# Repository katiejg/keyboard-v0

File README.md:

# keyboard_v0

## Guides Followed
- [Masterzen](https://www.masterzen.fr/tag/#mechanical-keyboards)
- [ai03](https://wiki.ai03.com/books/pcb-design)

## References
- [K6 Keycap Layout](https://www.keychron.com/pages/keychron-k6-keyboard-keycaps-layout-and-keycap-size-hd-picture)

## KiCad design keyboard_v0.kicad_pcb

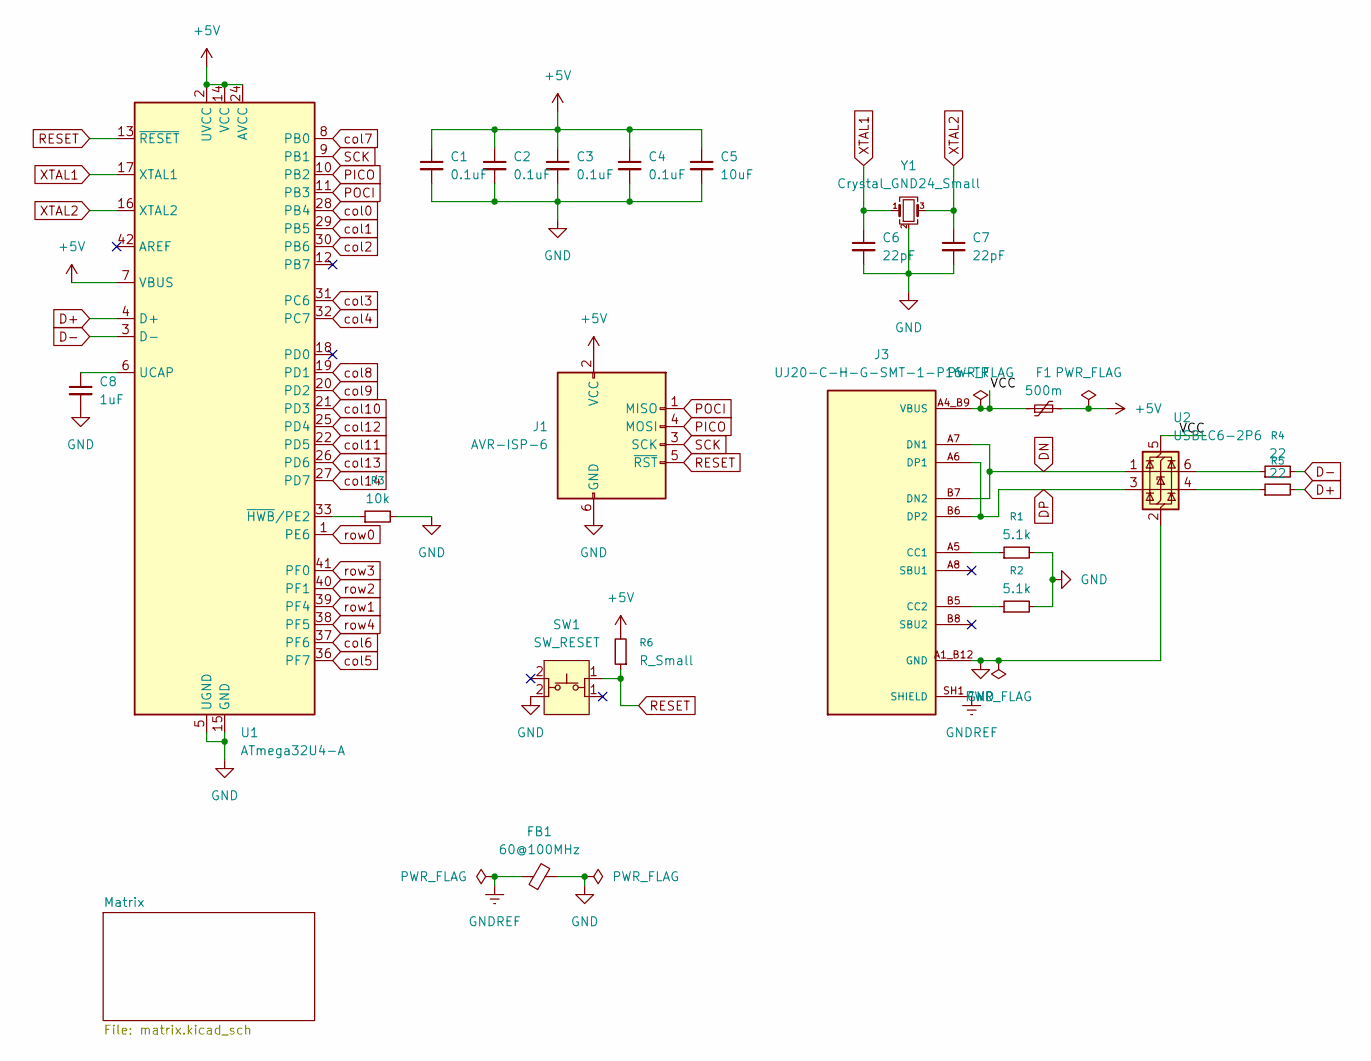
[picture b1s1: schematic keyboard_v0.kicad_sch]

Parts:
C1, C2, C3, C4: 0.1uF; C_0805_2012Metric_Pad1.18x1.45mm_HandSolder
C5: 10uF; C_0805_2012Metric_Pad1.18x1.45mm_HandSolder
C6, C7: 22pF; C_0805_2012Metric_Pad1.18x1.45mm_HandSolder
C8: 1uF; C_0805_2012Metric_Pad1.18x1.45mm_HandSolder
F1: 500m; Fuse_1206_3216Metric_Pad1.42x1.75mm_HandSolder
FB1: 60@100MHz; L_0805_2012Metric_Pad1.05x1.20mm_HandSolder
J1: AVR-ISP-6; Reset_Pretty-Mask
J3: UJ20-C-H-G-SMT-1-P16-TR; SAMESKY_UJ20-C-H-G-SMT-1-P16-TR; PARTREV 1.0; DigiKey_Part_Number 2223-UJ20-C-H-G-SMT-1-P16-TRCT-ND
R1, R2: 5.1k; R_0805_2012Metric_Pad1.20x1.40mm_HandSolder
R3: 10k; R_0805_2012Metric_Pad1.20x1.40mm_HandSolder
R4, R5: 22; R_0805_2012Metric_Pad1.20x1.40mm_HandSolder
R6: R_Small; R_0805_2012Metric_Pad1.20x1.40mm_HandSolder
SW1: SW_RESET; SW_SPST_SKQG_WithStem
U1: ATmega32U4-A; TQFP-44_10x10mm_P0.8mm
U2: USBLC6-2P6; SOT-666
Y1: Crystal_GND24_Small; Crystal_SMD_3225-4Pin_3.2x2.5mm_HandSoldering

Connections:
+5V: C1.1, C2.1, C3.1, C4.1, C5.1, F1.2, J1.2 (VCC), R6.2, U1.2 (UVCC), U1.7 (VBUS), U1.14 (VCC), U1.24 (AVCC), U1.34 (VCC), U1.44 (AVCC)
/VCC: F1.1, J3.A4_B9 (VBUS), J3.B4_A9 (VBUS), U2.5 (VBUS)
D+: R5.2, U1.4 (D+)
D-: R4.2, U1.3 (D-)
DN: J3.A7 (DN1), J3.B7 (DN2), U2.1 (I/O1)
DP: J3.A6 (DP1), J3.B6 (DP2), U2.3 (I/O2)
GND: C1.2, C2.2, C3.2, C4.2, C5.2, C6.2, C7.2, C8.2, FB1.2, J1.6 (GND), J3.A1_B12 (GND), J3.B1_A12 (GND), R1.2, R2.2, R3.2, SW1.2 (K), U1.5 (UGND), U1.15 (GND), U1.23 (GND), U1.35 (GND), U1.43 (GND), U2.2 (GND), Y1.2 (G), Y1.4 (G)
GNDREF: FB1.1, J3.SH1 (SHIELD), J3.SH2 (SHIELD), J3.SH3 (SHIELD), J3.SH4 (SHIELD)
unnamed: J3.A5 (CC1), R1.1
unnamed: J3.B5 (CC2), R2.1
unnamed: R4.1, U2.6 (I/O1)
unnamed: R5.1, U2.4 (I/O2)
unnamed: C8.1, U1.6 (UCAP)
unnamed: R3.1, U1.33 (~HWB/PE2)
PICO: J1.4 (MOSI), U1.10 (PB2)
POCI: J1.1 (MISO), U1.11 (PB3)
RESET: J1.5 (~RST), R6.1, SW1.1 (2), U1.13 (~RESET)
SCK: J1.3 (SCK), U1.9 (PB1)
XTAL1: C6.1, U1.17 (XTAL1), Y1.1
XTAL2: C7.1, U1.16 (XTAL2), Y1.3
col0: U1.28 (PB4); also elsewhere on the board
col1: U1.29 (PB5); also elsewhere on the board
col2: U1.30 (PB6); also elsewhere on the board
col3: U1.31 (PC6); also elsewhere on the board
col4: U1.32 (PC7); also elsewhere on the board
col5: U1.36 (PF7); also elsewhere on the board
col6: U1.37 (PF6); also elsewhere on the board
col7: U1.8 (PB0); also elsewhere on the board
col8: U1.19 (PD1); also elsewhere on the board
col9: U1.20 (PD2); also elsewhere on the board
col10: U1.21 (PD3); also elsewhere on the board
col11: U1.22 (PD5); also elsewhere on the board
col12: U1.25 (PD4); also elsewhere on the board
col13: U1.26 (PD6); also elsewhere on the board
col14: U1.27 (PD7); also elsewhere on the board
row0: U1.1 (PE6); also elsewhere on the board
row1: U1.39 (PF4); also elsewhere on the board
row2: U1.40 (PF1); also elsewhere on the board
row3: U1.41 (PF0); also elsewhere on the board
row4: U1.38 (PF5); also elsewhere on the board

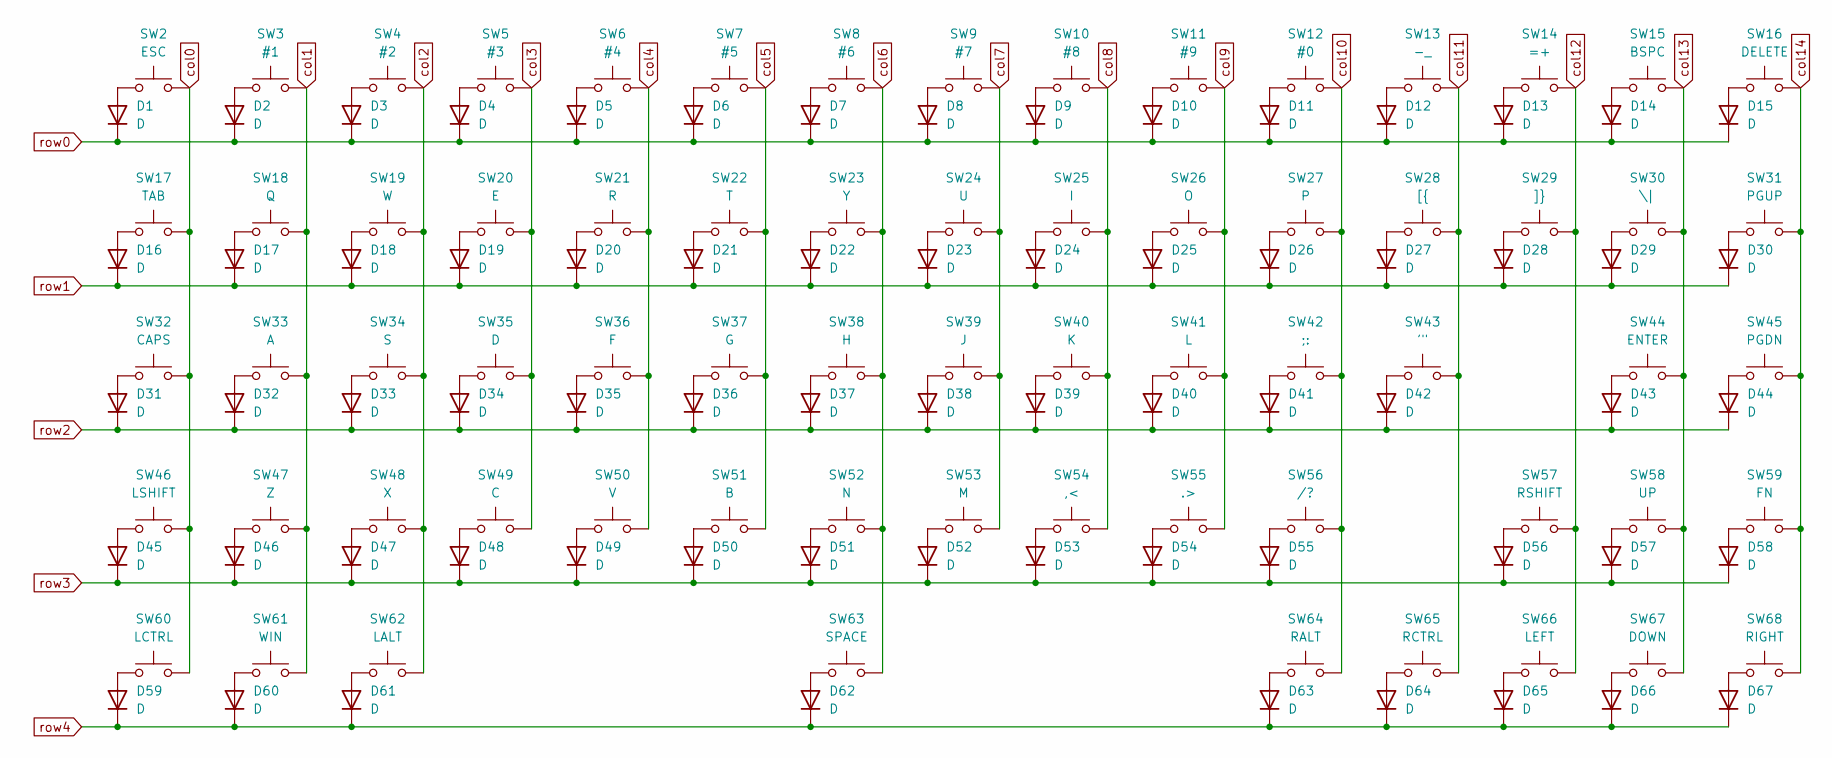
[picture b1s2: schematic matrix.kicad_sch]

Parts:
D1, D2, D3, D4, D5, D6, D7, D8, D9, D10, D11, D12, D13, D14, D15, D16, D17, D18, D19, D20, D21, D22, D23, D24, D25, D26, D27, D28, D29, D30, D31, D32, D33, D34, D35, D36, D37, D38, D39, D40, D41, D42, D43, D44, D45, D46, D47, D48, D49, D50, D51, D52, D53, D54, D55, D56, D57, D58, D59, D60, D61, D62, D63, D64, D65, D66, D67: D; D_SOD-123
SW2: ESC; MX-Hotswap-1U
SW3: #1; MX-Hotswap-1U
SW4: #2; MX-Hotswap-1U
SW5: #3; MX-Hotswap-1U
SW6: #4; MX-Hotswap-1U
SW7: #5; MX-Hotswap-1U
SW8: #6; MX-Hotswap-1U
SW9: #7; MX-Hotswap-1U
SW10: #8; MX-Hotswap-1U
SW11: #9; MX-Hotswap-1U
SW12: #0; MX-Hotswap-1U
SW13: -_; MX-Hotswap-1U
SW14: =+; MX-Hotswap-1U
SW15: BSPC; MX-Hotswap-2U
SW16: DELETE; MX-Hotswap-1U
SW17: TAB; MX-Hotswap-1.5U
SW18: Q; MX-Hotswap-1U
SW19: W; MX-Hotswap-1U
SW20: E; MX-Hotswap-1U
SW21: R; MX-Hotswap-1U
SW22: T; MX-Hotswap-1U
SW23: Y; MX-Hotswap-1U
SW24: U; MX-Hotswap-1U
SW25: I; MX-Hotswap-1U
SW26: O; MX-Hotswap-1U
SW27: P; MX-Hotswap-1U
SW28: [{; MX-Hotswap-1U
SW29: ]}; MX-Hotswap-1U
SW30: \|; MX-Hotswap-1.5U
SW31: PGUP; MX-Hotswap-1U
SW32: CAPS; MX-Hotswap-1.75U
SW33: A; MX-Hotswap-1U
SW34: S; MX-Hotswap-1U
SW35: D; MX-Hotswap-1U
SW36: F; MX-Hotswap-1U
SW37: G; MX-Hotswap-1U
SW38: H; MX-Hotswap-1U
SW39: J; MX-Hotswap-1U
SW40: K; MX-Hotswap-1U
SW41: L; MX-Hotswap-1U
SW42: ;:; MX-Hotswap-1U
SW43: '"; MX-Hotswap-1U
SW44: ENTER; MX-Hotswap-2.25U
SW45: PGDN; MX-Hotswap-1U
SW46: LSHIFT; MX-Hotswap-2.25U
SW47: Z; MX-Hotswap-1U
SW48: X; MX-Hotswap-1U
SW49: C; MX-Hotswap-1U
SW50: V; MX-Hotswap-1U
SW51: B; MX-Hotswap-1U
SW52: N; MX-Hotswap-1U
SW53: M; MX-Hotswap-1U
SW54: ,<; MX-Hotswap-1U
SW55: .>; MX-Hotswap-1U
SW56: /?; MX-Hotswap-1U
SW57: RSHIFT; MX-Hotswap-1.75U
SW58: UP; MX-Hotswap-1U
SW59: FN; MX-Hotswap-1U
SW60: LCTRL; MX-Hotswap-1.25U
SW61: WIN; MX-Hotswap-1.25U
SW62: LALT; MX-Hotswap-1.25U
SW63: SPACE; MX-Hotswap-6.25U
SW64: RALT; MX-Hotswap-1.25U
SW65: RCTRL; MX-Hotswap-1.25U
SW66: LEFT; MX-Hotswap-1U
SW67: DOWN; MX-Hotswap-1U
SW68: RIGHT; MX-Hotswap-1U

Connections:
unnamed: D1.2 (A), SW2.1
unnamed: D2.2 (A), SW3.1
unnamed: D3.2 (A), SW4.1
unnamed: D4.2 (A), SW5.1
unnamed: D5.2 (A), SW6.1
unnamed: D6.2 (A), SW7.1
unnamed: D7.2 (A), SW8.1
unnamed: D8.2 (A), SW9.1
unnamed: D9.2 (A), SW10.1
unnamed: D10.2 (A), SW11.1
unnamed: D11.2 (A), SW12.1
unnamed: D12.2 (A), SW13.1
unnamed: D13.2 (A), SW14.1
unnamed: D14.2 (A), SW15.1
unnamed: D15.2 (A), SW16.1
unnamed: D16.2 (A), SW17.1
unnamed: D17.2 (A), SW18.1
unnamed: D18.2 (A), SW19.1
unnamed: D19.2 (A), SW20.1
unnamed: D20.2 (A), SW21.1
unnamed: D21.2 (A), SW22.1
unnamed: D22.2 (A), SW23.1
unnamed: D23.2 (A), SW24.1
unnamed: D24.2 (A), SW25.1
unnamed: D25.2 (A), SW26.1
unnamed: D26.2 (A), SW27.1
unnamed: D27.2 (A), SW28.1
unnamed: D28.2 (A), SW29.1
unnamed: D29.2 (A), SW30.1
unnamed: D30.2 (A), SW31.1
unnamed: D31.2 (A), SW32.1
unnamed: D32.2 (A), SW33.1
unnamed: D33.2 (A), SW34.1
unnamed: D34.2 (A), SW35.1
unnamed: D35.2 (A), SW36.1
unnamed: D36.2 (A), SW37.1
unnamed: D37.2 (A), SW38.1
unnamed: D38.2 (A), SW39.1
unnamed: D39.2 (A), SW40.1
unnamed: D40.2 (A), SW41.1
unnamed: D41.2 (A), SW42.1
unnamed: D42.2 (A), SW43.1
unnamed: D43.2 (A), SW44.1
unnamed: D44.2 (A), SW45.1
unnamed: D45.2 (A), SW46.1
unnamed: D46.2 (A), SW47.1
unnamed: D47.2 (A), SW48.1
unnamed: D48.2 (A), SW49.1
unnamed: D49.2 (A), SW50.1
unnamed: D50.2 (A), SW51.1
unnamed: D51.2 (A), SW52.1
unnamed: D52.2 (A), SW53.1
unnamed: D53.2 (A), SW54.1
unnamed: D54.2 (A), SW55.1
unnamed: D55.2 (A), SW56.1
unnamed: D56.2 (A), SW57.1
unnamed: D57.2 (A), SW58.1
unnamed: D58.2 (A), SW59.1
unnamed: D59.2 (A), SW60.1
unnamed: D60.2 (A), SW61.1
unnamed: D61.2 (A), SW62.1
unnamed: D62.2 (A), SW63.1
unnamed: D63.2 (A), SW64.1
unnamed: D64.2 (A), SW65.1
unnamed: D65.2 (A), SW66.1
unnamed: D66.2 (A), SW67.1
unnamed: D67.2 (A), SW68.1
col0: SW2.2, SW17.2, SW32.2, SW46.2, SW60.2; also elsewhere on the board
col1: SW3.2, SW18.2, SW33.2, SW47.2, SW61.2; also elsewhere on the board
col2: SW4.2, SW19.2, SW34.2, SW48.2, SW62.2; also elsewhere on the board
col3: SW5.2, SW20.2, SW35.2, SW49.2; also elsewhere on the board
col4: SW6.2, SW21.2, SW36.2, SW50.2; also elsewhere on the board
col5: SW7.2, SW22.2, SW37.2, SW51.2; also elsewhere on the board
col6: SW8.2, SW23.2, SW38.2, SW52.2, SW63.2; also elsewhere on the board
col7: SW9.2, SW24.2, SW39.2, SW53.2; also elsewhere on the board
col8: SW10.2, SW25.2, SW40.2, SW54.2; also elsewhere on the board
col9: SW11.2, SW26.2, SW41.2, SW55.2; also elsewhere on the board
col10: SW12.2, SW27.2, SW42.2, SW56.2, SW64.2; also elsewhere on the board
col11: SW13.2, SW28.2, SW43.2, SW65.2; also elsewhere on the board
col12: SW14.2, SW29.2, SW57.2, SW66.2; also elsewhere on the board
col13: SW15.2, SW30.2, SW44.2, SW58.2, SW67.2; also elsewhere on the board
col14: SW16.2, SW31.2, SW45.2, SW59.2, SW68.2; also elsewhere on the board
row0: D1.1 (K), D2.1 (K), D3.1 (K), D4.1 (K), D5.1 (K), D6.1 (K), D7.1 (K), D8.1 (K), D9.1 (K), D10.1 (K), D11.1 (K), D12.1 (K), D13.1 (K), D14.1 (K), D15.1 (K); also elsewhere on the board
row1: D16.1 (K), D17.1 (K), D18.1 (K), D19.1 (K), D20.1 (K), D21.1 (K), D22.1 (K), D23.1 (K), D24.1 (K), D25.1 (K), D26.1 (K), D27.1 (K), D28.1 (K), D29.1 (K), D30.1 (K); also elsewhere on the board
row2: D31.1 (K), D32.1 (K), D33.1 (K), D34.1 (K), D35.1 (K), D36.1 (K), D37.1 (K), D38.1 (K), D39.1 (K), D40.1 (K), D41.1 (K), D42.1 (K), D43.1 (K), D44.1 (K); also elsewhere on the board
row3: D45.1 (K), D46.1 (K), D47.1 (K), D48.1 (K), D49.1 (K), D50.1 (K), D51.1 (K), D52.1 (K), D53.1 (K), D54.1 (K), D55.1 (K), D56.1 (K), D57.1 (K), D58.1 (K); also elsewhere on the board
row4: D59.1 (K), D60.1 (K), D61.1 (K), D62.1 (K), D63.1 (K), D64.1 (K), D65.1 (K), D66.1 (K), D67.1 (K); also elsewhere on the board

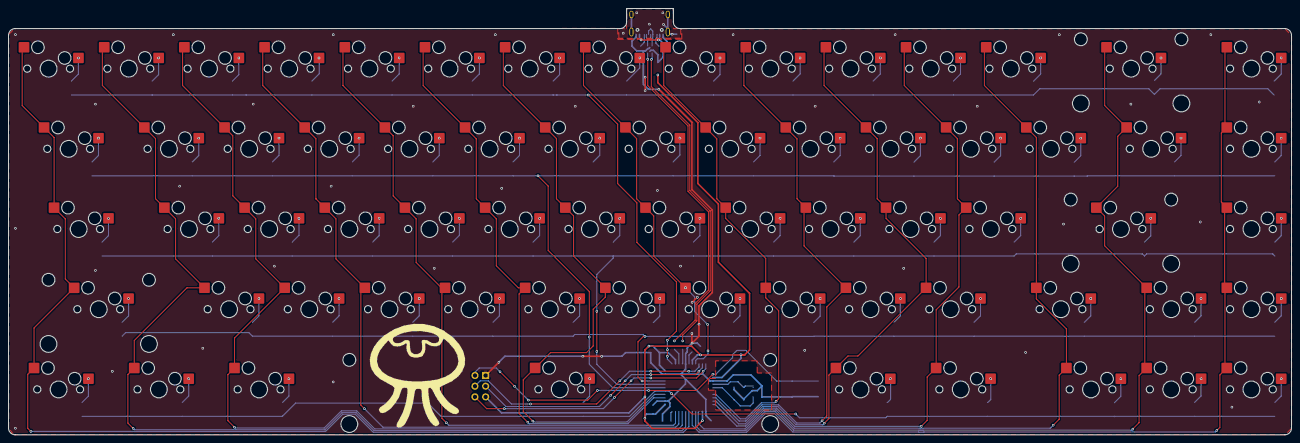
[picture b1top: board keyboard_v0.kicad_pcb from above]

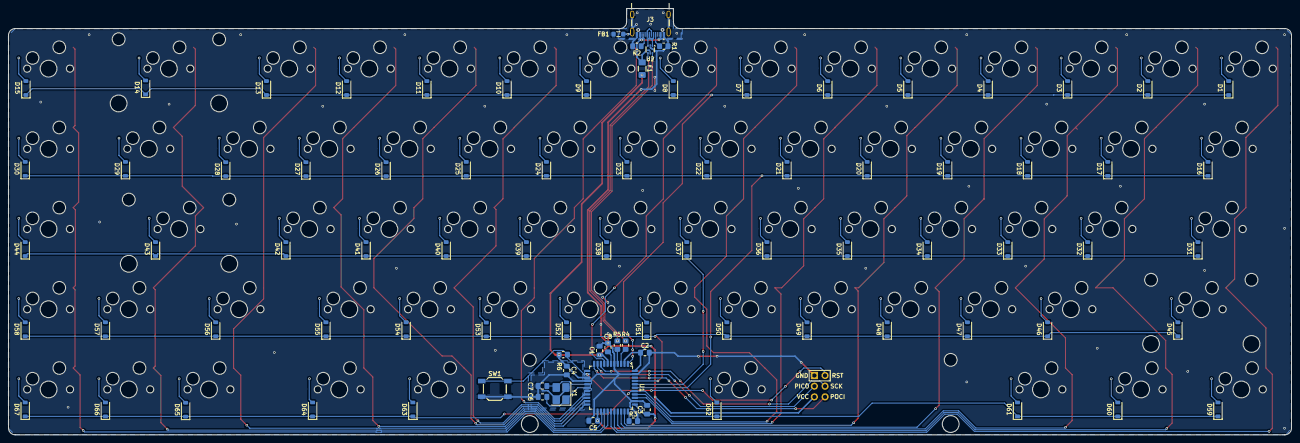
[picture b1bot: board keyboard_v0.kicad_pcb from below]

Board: 2 copper layers, 304.8 x 101.3 mm, 156 parts (89 on the bottom side), 107 nets.
